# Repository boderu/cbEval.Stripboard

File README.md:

# cbEval.Stripboard

Evaluation-Board - basierend auf dem modularen Gehäuse von Camdenboss. Lochraster.

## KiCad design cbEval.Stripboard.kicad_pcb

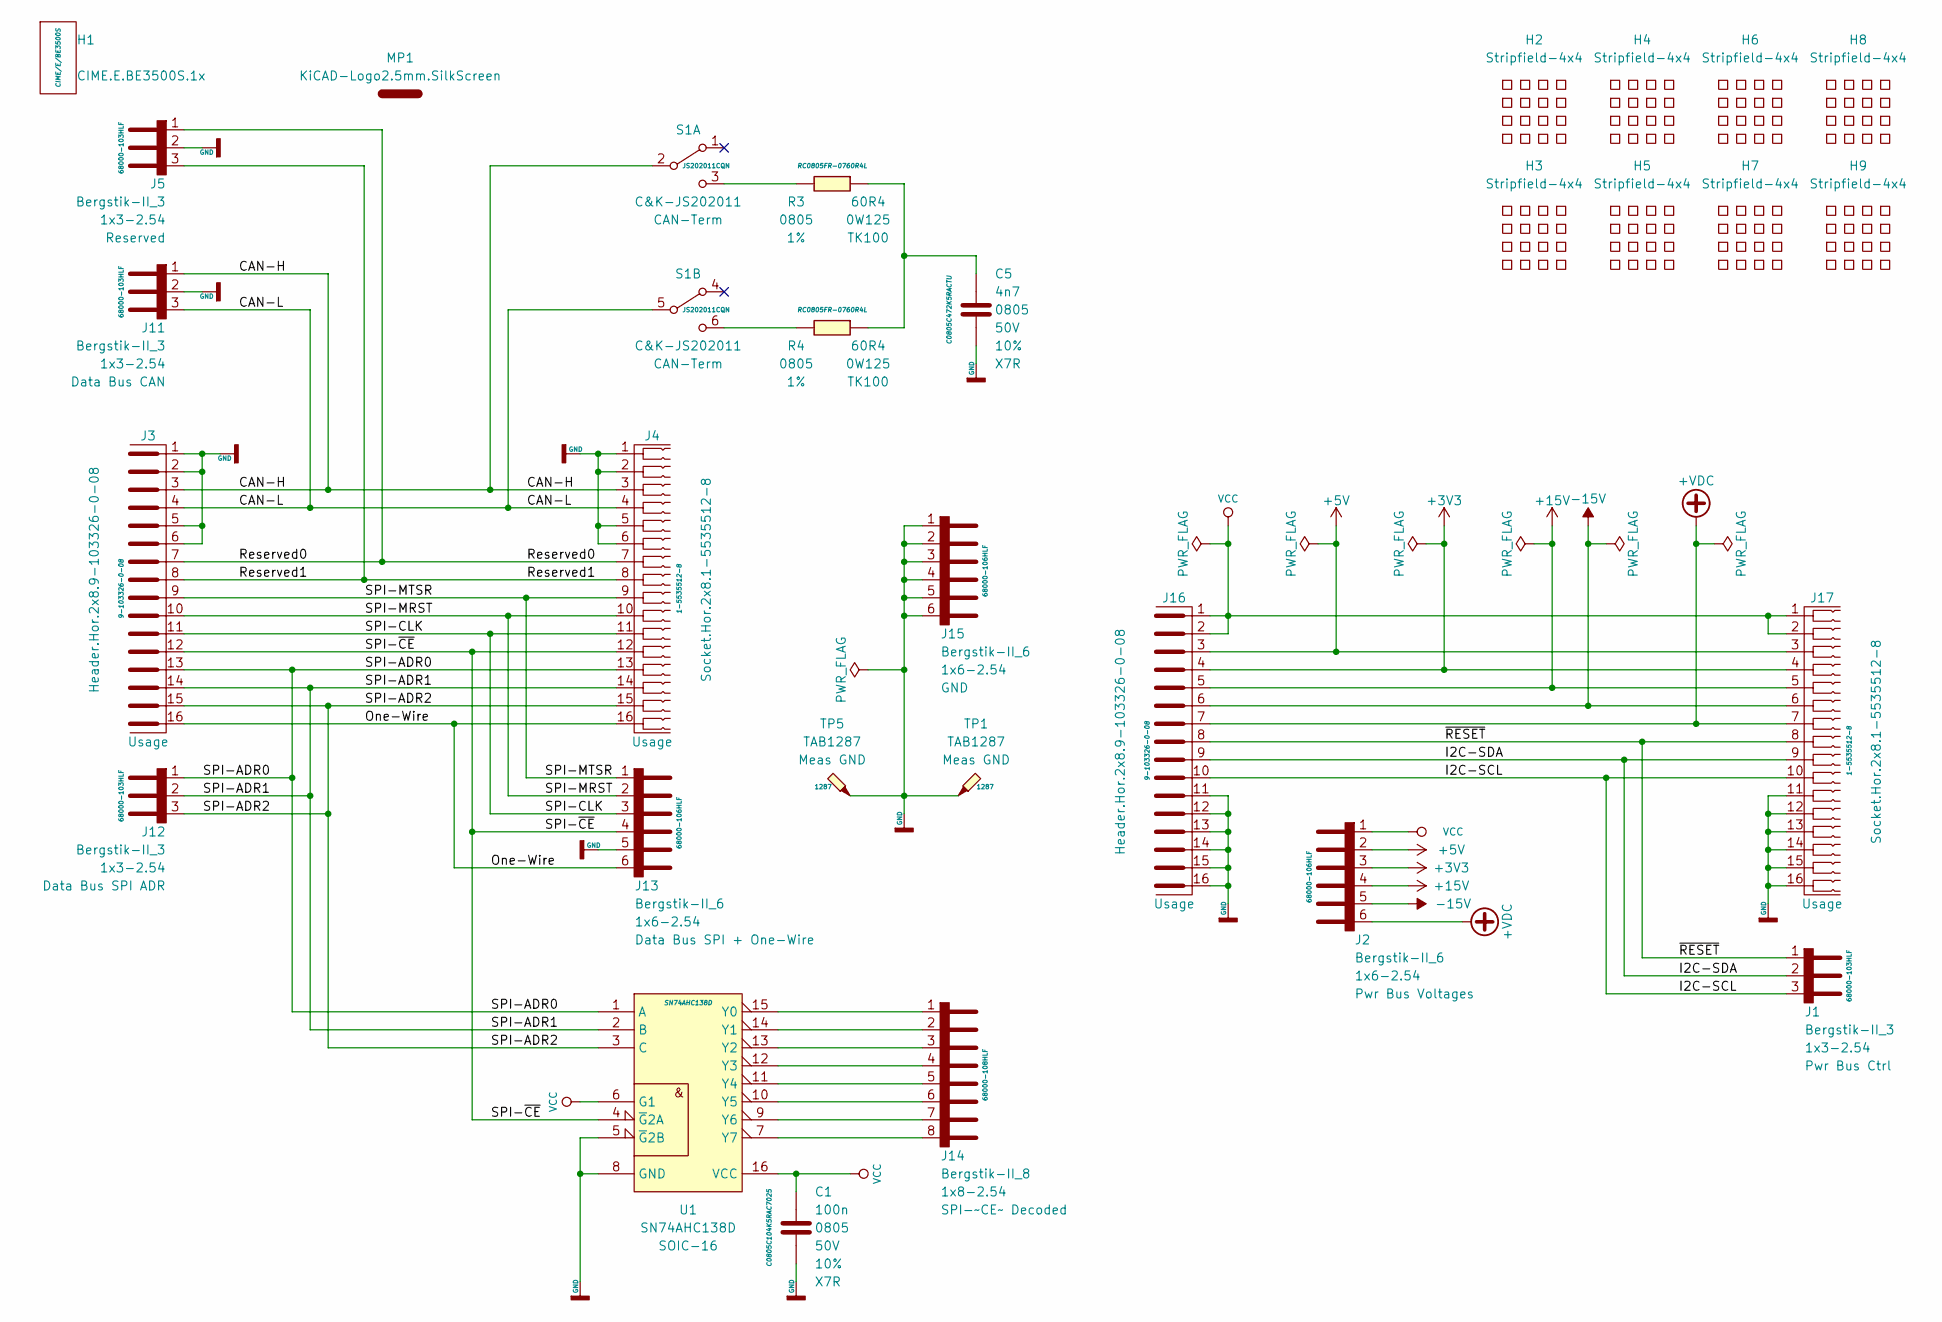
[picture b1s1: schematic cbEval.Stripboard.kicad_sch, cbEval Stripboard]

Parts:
C1: 100n; C_0805_2012Metric; Voltage 50V; Tolerance 10%
C5: 4n7; C_0805_2012Metric; Voltage 50V; Tolerance 10%
H1: CIME.E.BE3500S.1x; Camdenboss.CIME.E.BE3500S.1x
H2, H3, H4, H5, H6, H7, H8, H9: Stripfield-4x4
J1, J5, J11, J12: Bergstik-II_3; PinHeader_1x03_P2.54mm_Vertical
J2, J13, J15: Bergstik-II_6; PinHeader_1x06_P2.54mm_Vertical
J3, J16: Header.Hor.2x8.9-103326-0-08; PinHeader_2x08_P2.54mm_Horizontal
J4, J17: Socket.Hor.2x8.1-5535512-8; Socket.Hor.2x5.6-5535512-4
J14: Bergstik-II_8; PinHeader_1x08_P2.54mm_Vertical
MP1: KiCAD-Logo2.5mm.SilkScreen; KiCad-Logo_5mm_SilkScreen
R3, R4: 60R4; R_0805_2012Metric; Tolerance 1%
S1: C&K-JS202011; SW_CuK_JS202011CQN_DPDT_Straight
TP1, TP5: TAB1287; TestPoint_Bridge_Pitch5.08mm_Drill1.3mm
U1: SN74AHC138D; SOIC-16_3.9x9.9mm_P1.27mm

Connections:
+3V3: J2.3 (A3), J16.4, J17.4
+5V: J2.2 (A2), J16.3, J17.3
+15V: J2.4 (A4), J16.5, J17.5
+VDC: J2.6 (A6), J16.7, J17.7
-15V: J2.5 (A5), J16.6, J17.6
/CAN-H: J3.3, J4.3, J11.1 (A1), S1.2 (B)
/CAN-L: J3.4, J4.4, J11.3 (A3), S1.5 (B)
/I2C-SCL: J1.3 (A3), J16.10, J17.10
/I2C-SDA: J1.2 (A2), J16.9, J17.9
/One-Wire: J3.16, J4.16, J13.6 (A6)
/Reserved0: J3.7, J4.7, J5.1 (A1)
/Reserved1: J3.8, J4.8, J5.3 (A3)
/SPI-ADR0: J3.13, J4.13, J12.1 (A1), U1.1 (A)
/SPI-ADR1: J3.14, J4.14, J12.2 (A2), U1.2 (B)
/SPI-ADR2: J3.15, J4.15, J12.3 (A3), U1.3 (C)
/SPI-CLK: J3.11, J4.11, J13.3 (A3)
/SPI-MRST: J3.10, J4.10, J13.2 (A2)
/SPI-MTSR: J3.9, J4.9, J13.1 (A1)
/SPI-~CE: J3.12, J4.12, J13.4 (A4), U1.4 (~G~2A)
/~RESET: J1.1 (A1), J16.8, J17.8
GND: C1.2, C5.2, J3.1, J3.2, J3.5, J3.6, J4.1, J4.2, J4.5, J4.6, J5.2 (A2), J11.2 (A2), J13.5 (A5), J15.1 (A1), J15.2 (A2), J15.3 (A3), J15.4 (A4), J15.5 (A5), J15.6 (A6), J16.11, J16.12, J16.13, J16.14, J16.15, J16.16, J17.11, J17.12, J17.13, J17.14, J17.15, J17.16, TP1.1, TP5.1, U1.5 (~G~2B), U1.8 (GND)
unnamed: C5.1, R3.1, R4.1
unnamed: J14.1 (A1), U1.15 (Y0)
unnamed: J14.2 (A2), U1.14 (Y1)
unnamed: J14.3 (A3), U1.13 (Y2)
unnamed: J14.4 (A4), U1.12 (Y3)
unnamed: J14.5 (A5), U1.11 (Y4)
unnamed: J14.6 (A6), U1.10 (Y5)
unnamed: J14.7 (A7), U1.9 (Y6)
unnamed: J14.8 (A8), U1.7 (Y7)
unnamed: R3.2, S1.3 (C)
unnamed: R4.2, S1.6 (C)
VCC: C1.1, J2.1 (A1), J16.1, J16.2, J17.1, J17.2, U1.6 (G1), U1.16 (VCC)

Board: 2 copper layers, 30 parts (0 on the bottom side), 33 nets, no tracks yet.

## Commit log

2021-04-04 grobe Platzierung fertig
2021-04-05 kleinere Korrekturen
2021-04-06 kleinere Änderungen
2021-04-11 Bus-Stecker getauscht, BOM erstellt
2023-11-08 Update auf KiCAD-Version 7
